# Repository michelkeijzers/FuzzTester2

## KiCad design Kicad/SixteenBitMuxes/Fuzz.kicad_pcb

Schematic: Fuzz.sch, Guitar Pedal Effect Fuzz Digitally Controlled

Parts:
C1: 22uF; CP_Radial_D5.0mm_P2.50mm
H1, H2, H3, H4: MountingHole; MountingHole_3.2mm_M3
J2: TONE_POTS; JST_XH_B4B-XH-A_1x04_P2.50mm_Vertical
J4: VOL POT A100K JST XH; JST_XH_B3B-XH-A_1x03_P2.50mm_Vertical
R1, R2: 100K; R_1206_3216Metric_Pad1.42x1.75mm_HandSolder
R3: 10K; R_1206_3216Metric_Pad1.42x1.75mm_HandSolder

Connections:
/+9V_SAFE: R1.1, R3.1; also elsewhere on the board
/B10K: J2.1, J2.3, R2.1; also elsewhere on the board
/CapacitorsD/CAPACITOR_AUDIO_INPUT: R3.2; also elsewhere on the board
/CapacitorsD/CAPACITOR_AUDIO_OUTPUT: J4.3; also elsewhere on the board
/JACK_OUT_SIGNAL_FROM_FUZZ: J4.2; also elsewhere on the board
/TransistorsB/BASE: R2.2; also elsewhere on the board
/TransistorsC/BASE: R1.2; also elsewhere on the board
GND: H1.1, H4.1; also elsewhere on the board
GNDA: C1.2, H2.1, H3.1, J2.2, J4.1; also elsewhere on the board
unnamed: C1.1, J2.4

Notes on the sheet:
Fuzz Analog Circuit
Audio In/Out and Bypass
Level Shifters
Power Regulator
Micro Controller Unit and User Interface
Mounting Holes

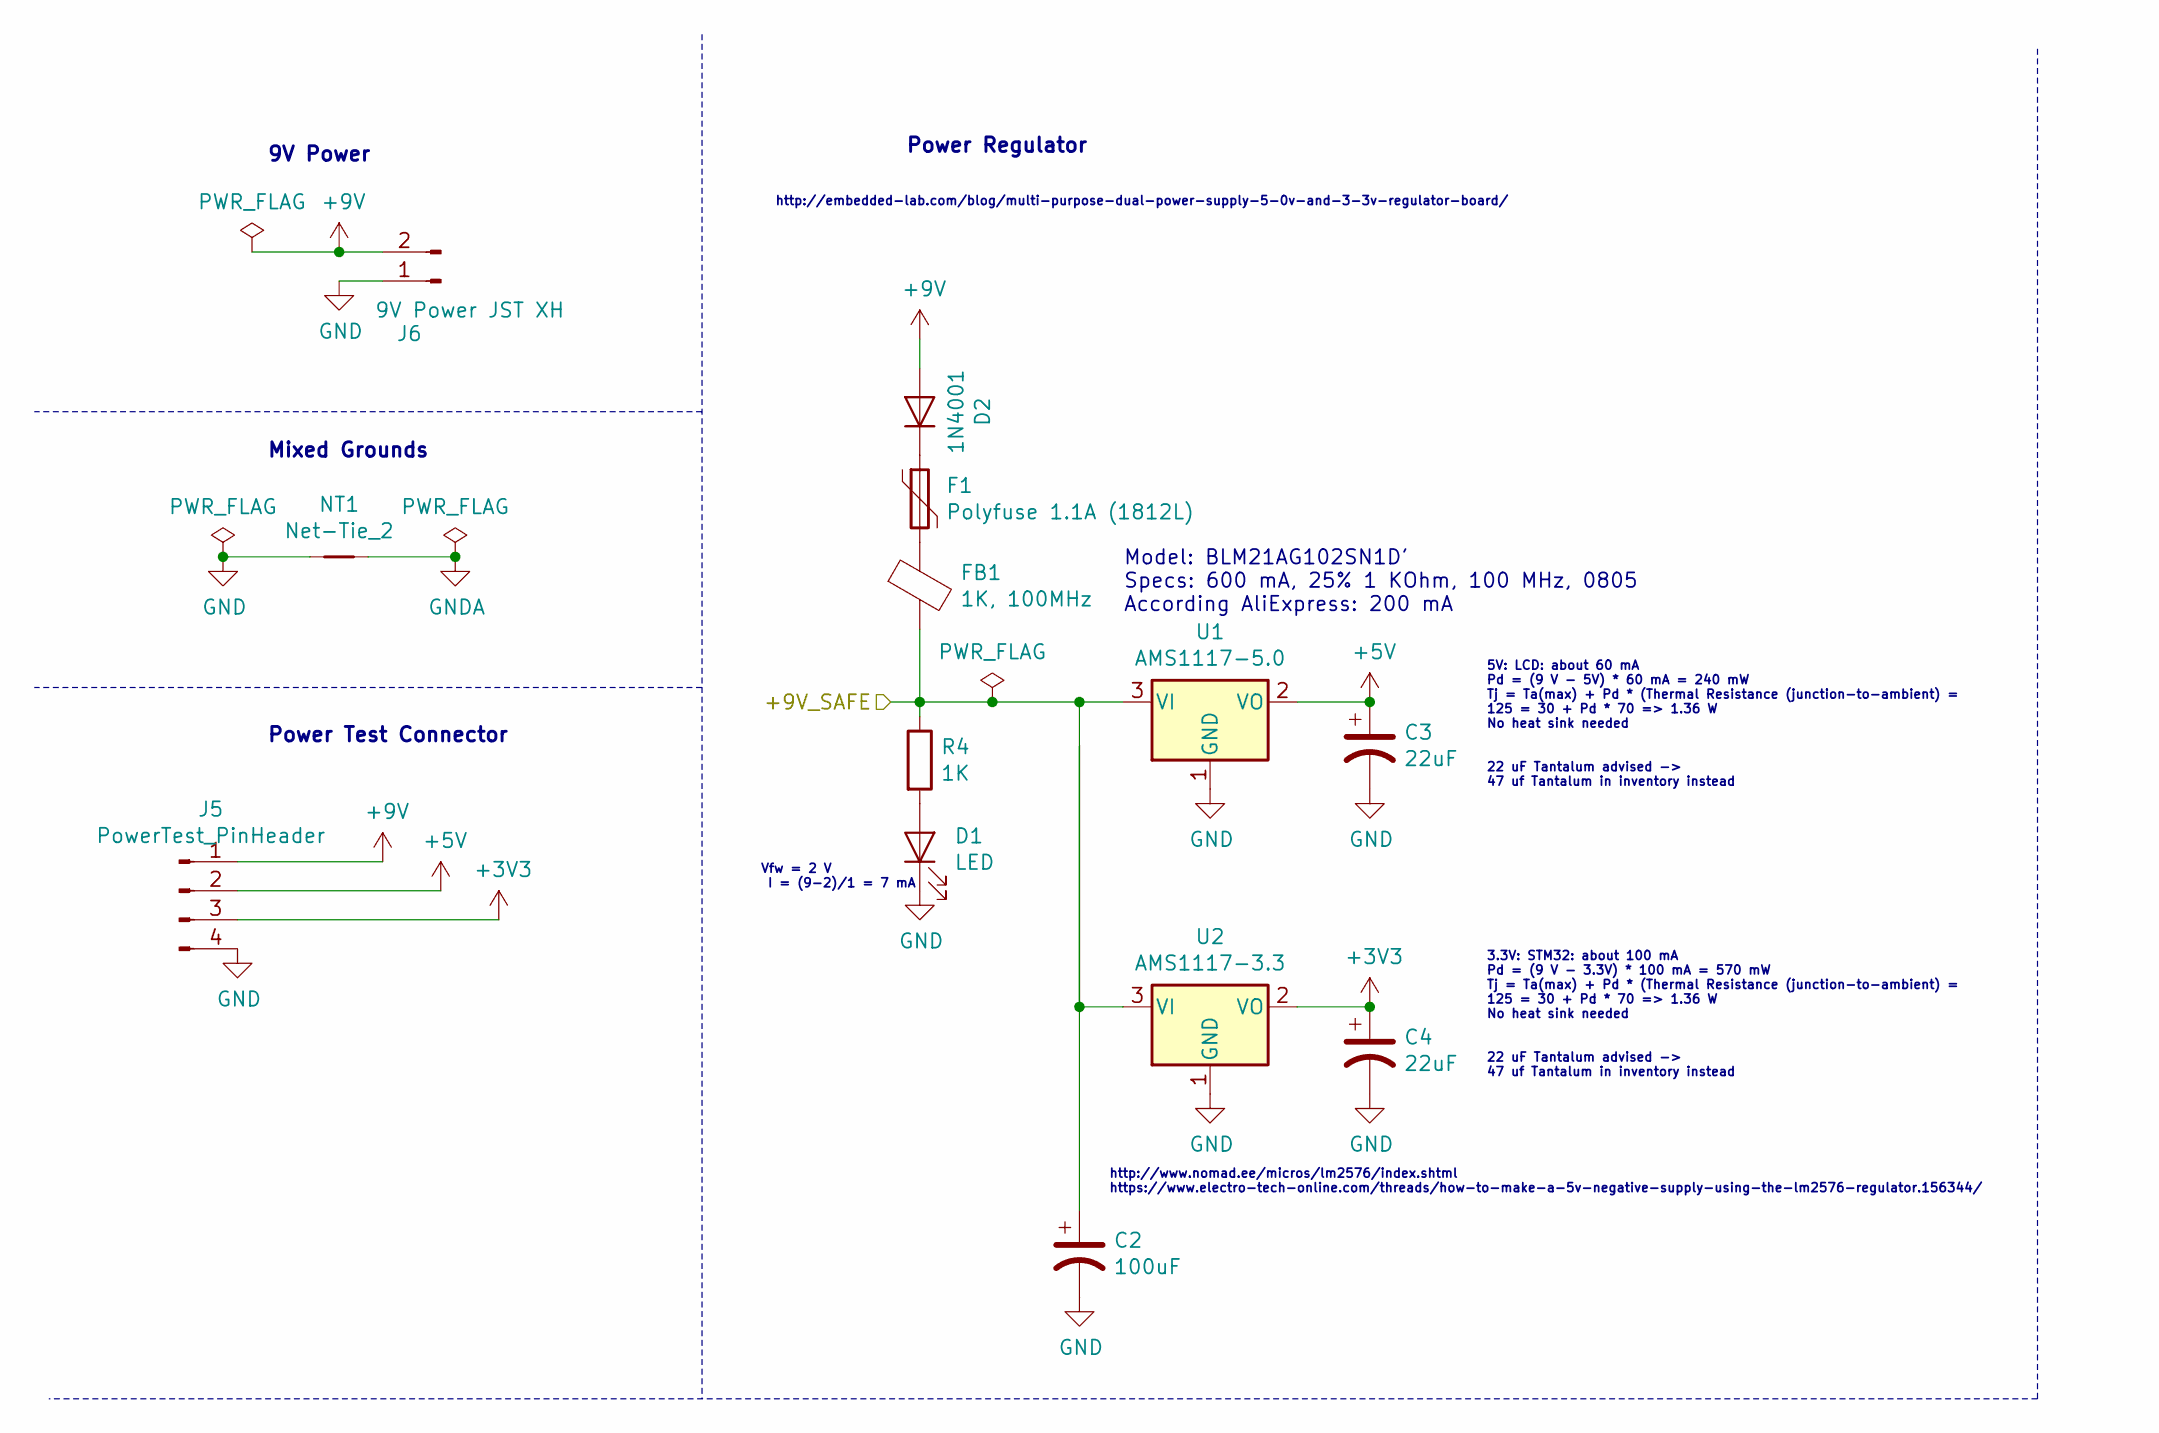
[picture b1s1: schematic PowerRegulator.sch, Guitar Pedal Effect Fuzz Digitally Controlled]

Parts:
C2: 100uF; CP_Radial_D5.0mm_P2.50mm
C3, C4: 22uF; D_SMB_Handsoldering
D1: LED; LED_0805_2012Metric_Pad1.15x1.40mm_HandSolder
D2: 1N4001; D_0805_2012Metric_Pad1.15x1.40mm_HandSolder
F1: Polyfuse 1.1A (1812L); L_1812_4532Metric_Pad1.30x3.40mm_HandSolder
FB1: 1K, 100MHz; L_0805_2012Metric_Pad1.15x1.40mm_HandSolder
J5: PowerTest_PinHeader; PinHeader_1x04_P2.54mm_Vertical
J6: 9V Power JST XH; JST_XH_B2B-XH-A_1x02_P2.50mm_Vertical
NT1: Net-Tie_2; NetTie-2_SMD_Pad2.0mm
R4: 1K; R_0805_2012Metric_Pad1.15x1.40mm_HandSolder
U1: AMS1117-5.0; SOT-223-3_TabPin2
U2: AMS1117-3.3; SOT-223-3_TabPin2

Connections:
+3V3: C4.1, J5.3, U2.2 (VO); also elsewhere on the board
+5V: C3.1, J5.2, U1.2 (VO); also elsewhere on the board
+9V: D2.2 (A), J5.1, J6.2
/+9V_SAFE: C2.1, FB1.2, R4.1, U1.3 (VI), U2.3 (VI); also elsewhere on the board
GND: C2.2, C3.2, C4.2, D1.1 (K), J5.4, J6.1, NT1.1, U1.1 (GND), U2.1 (GND); also elsewhere on the board
GNDA: NT1.2; also elsewhere on the board
unnamed: D1.2 (A), R4.2
unnamed: D2.1 (K), F1.1
unnamed: F1.2, FB1.1

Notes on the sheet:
9V Power
Vfw = 2 V I = (9-2)/1 = 7 mA
5V: LCD: about 60 mA Pd = (9 V - 5V) * 60 mA = 240 mW Tj = Ta(max) + Pd * (Thermal Resistance (junction-to-ambient) = 125 = 30 + Pd * 70 => 1.36 W No heat sink needed
3.3V: STM32: about 100 mA Pd = (9 V - 3.3V) * 100 mA = 570 mW Tj = Ta(max) + Pd * (Thermal Resistance (junction-to-ambient) = 125 = 30 + Pd * 70 => 1.36 W No heat sink needed
Power Regulator
http://embedded-lab.com/blog/multi-purpose-dual-power-supply-5-0v-and-3-3v-regulator-board/
https://www.electro-tech-online.com/threads/how-to-make-a-5v-negative-supply-using-the-lm2576-regulator.156344/
http://www.nomad.ee/micros/lm2576/index.shtml
Power Test Connector
Mixed Grounds
22 uF Tantalum advised -> 47 uf Tantalum in inventory instead
Model: BLM21AG102SN1D' Specs: 600 mA, 25% 1 KOhm, 100 MHz, 0805 According AliExpress: 200 mA

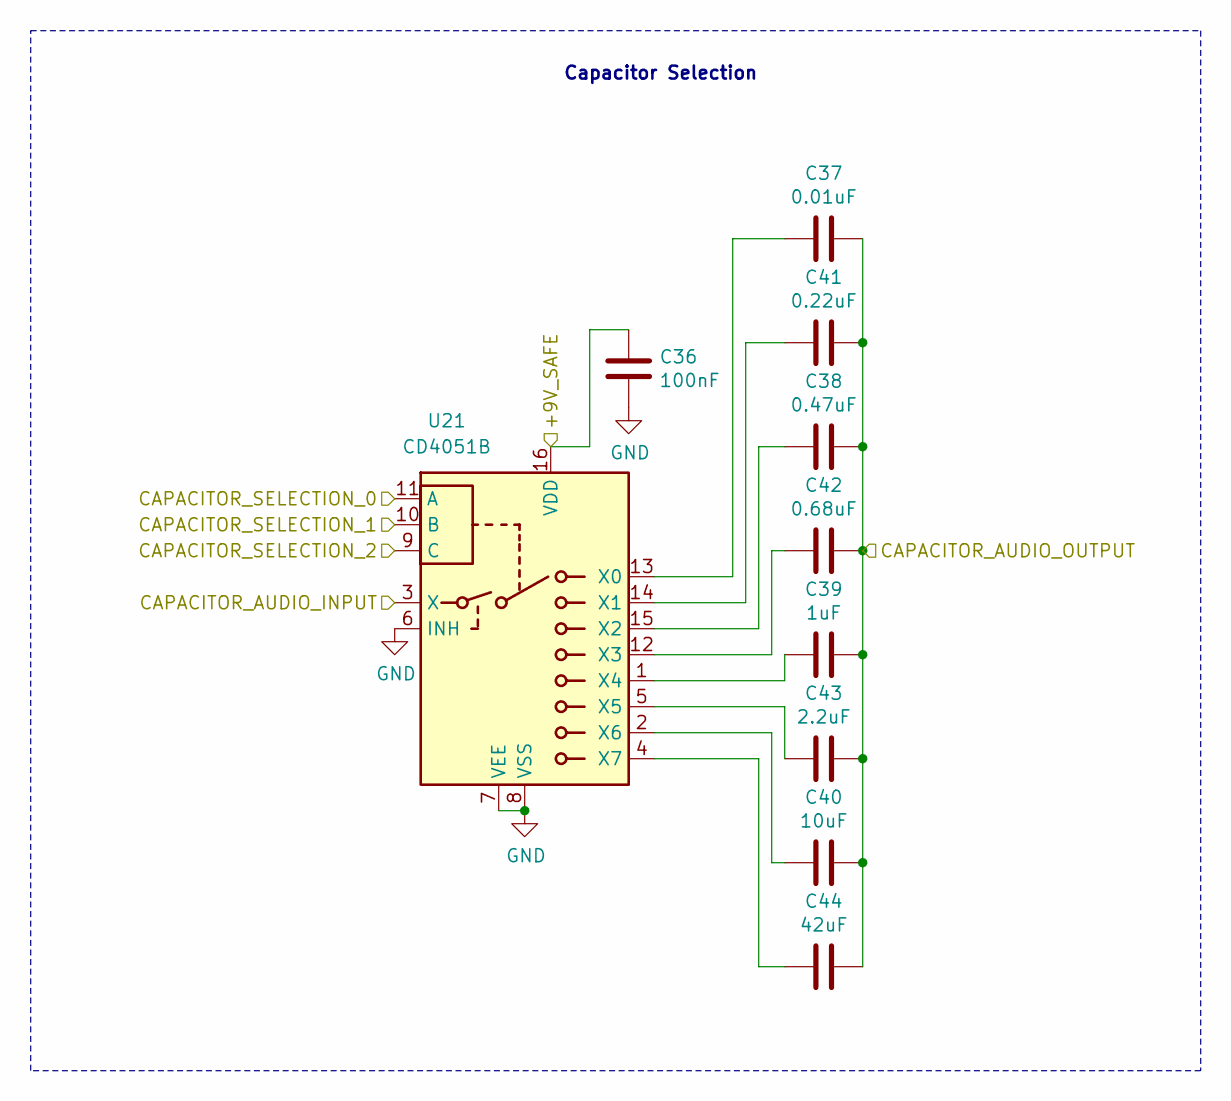
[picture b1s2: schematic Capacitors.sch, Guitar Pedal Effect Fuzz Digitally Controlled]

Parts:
C11: 100nF; C_0805_2012Metric_Pad1.15x1.40mm_HandSolder
C12: 0.01uF; C_0805_2012Metric_Pad1.15x1.40mm_HandSolder
C13: 0.47uF; C_0805_2012Metric_Pad1.15x1.40mm_HandSolder
C14: 1uF; C_0805_2012Metric_Pad1.15x1.40mm_HandSolder
C15: 10uF; C_0805_2012Metric_Pad1.15x1.40mm_HandSolder
C16: 0.22uF; C_0805_2012Metric_Pad1.15x1.40mm_HandSolder
C17: 0.68uF; C_0805_2012Metric_Pad1.15x1.40mm_HandSolder
C18: 2.2uF; C_0805_2012Metric_Pad1.15x1.40mm_HandSolder
C19: 42uF; C_0805_2012Metric_Pad1.15x1.40mm_HandSolder
U4: CD4051B; SOIC-16_3.9x9.9mm_P1.27mm

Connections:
/+9V_SAFE: C11.1, U4.16 (VDD); also elsewhere on the board
/CAPACITOR_A_SELECTION_0: U4.11 (A); also elsewhere on the board
/CAPACITOR_A_SELECTION_1: U4.10 (B); also elsewhere on the board
/CAPACITOR_A_SELECTION_2: U4.9 (C); also elsewhere on the board
/JACK_IN_SIGNAL_THROUGH_FUZZ: U4.3 (X); also elsewhere on the board
/TransistorsB/BASE: C12.1, C13.1, C14.1, C15.1, C16.1, C17.1, C18.1, C19.1; also elsewhere on the board
GND: C11.2, U4.6 (INH), U4.7 (VEE), U4.8 (VSS); also elsewhere on the board
unnamed: C12.2, U4.13 (X0)
unnamed: C13.2, U4.15 (X2)
unnamed: C14.2, U4.1 (X4)
unnamed: C15.2, U4.2 (X6)
unnamed: C16.2, U4.14 (X1)
unnamed: C17.2, U4.12 (X3)
unnamed: C18.2, U4.5 (X5)
unnamed: C19.2, U4.4 (X7)

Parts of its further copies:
C36: 100nF; C_0805_2012Metric_Pad1.15x1.40mm_HandSolder
C37: 0.01uF; C_0805_2012Metric_Pad1.15x1.40mm_HandSolder
C38: 0.47uF; C_0805_2012Metric_Pad1.15x1.40mm_HandSolder
C39: 1uF; C_0805_2012Metric_Pad1.15x1.40mm_HandSolder
C40: 10uF; C_0805_2012Metric_Pad1.15x1.40mm_HandSolder
C41: 0.22uF; C_0805_2012Metric_Pad1.15x1.40mm_HandSolder
C42: 0.68uF; C_0805_2012Metric_Pad1.15x1.40mm_HandSolder
C43: 2.2uF; C_0805_2012Metric_Pad1.15x1.40mm_HandSolder
C44: 42uF; C_0805_2012Metric_Pad1.15x1.40mm_HandSolder

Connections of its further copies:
/+9V_SAFE: C36.1; also elsewhere on the board
/CapacitorsD/CAPACITOR_AUDIO_OUTPUT: C37.1, C38.1, C39.1, C40.1, C41.1, C42.1, C43.1, C44.1; also elsewhere on the board
GND: C36.2; also elsewhere on the board
unnamed 139: C37.2; also elsewhere on the board
unnamed 140: C38.2; also elsewhere on the board
unnamed 141: C39.2; also elsewhere on the board
unnamed 142: C40.2; also elsewhere on the board
unnamed 143: C41.2; also elsewhere on the board
unnamed 144: C42.2; also elsewhere on the board
unnamed 145: C43.2; also elsewhere on the board
unnamed 146: C44.2; also elsewhere on the board

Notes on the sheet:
Capacitor Selection

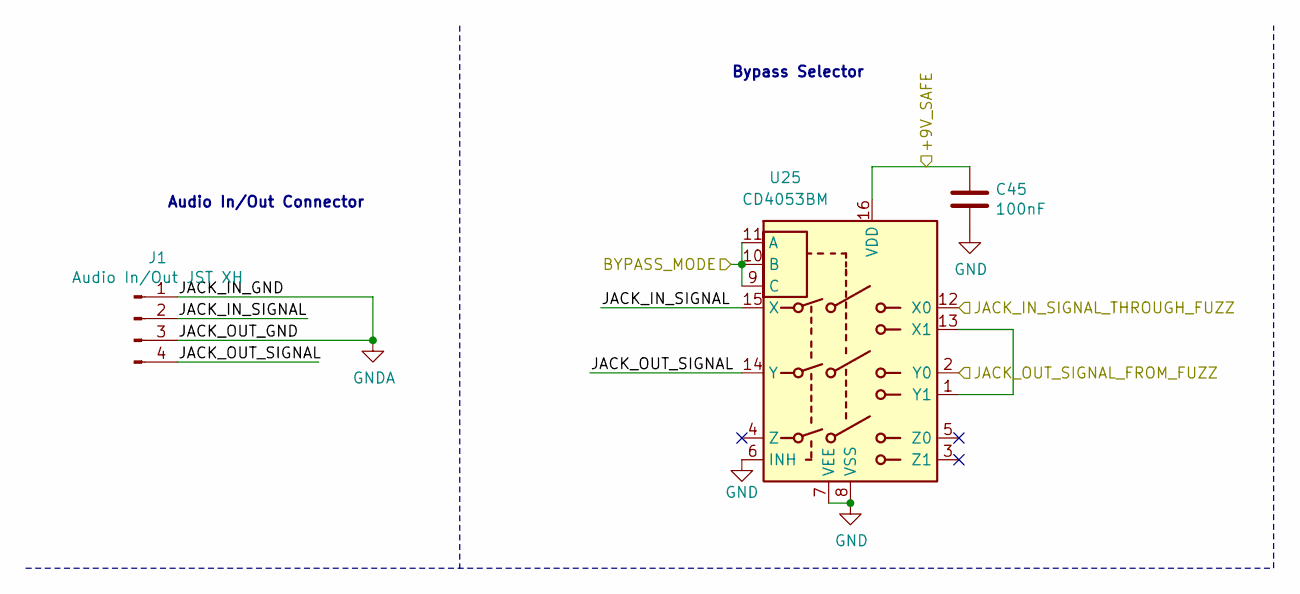
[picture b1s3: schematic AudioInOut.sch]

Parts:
C45: 100nF; C_0805_2012Metric_Pad1.15x1.40mm_HandSolder
J1: Audio In/Out JST XH; JST_XH_B4B-XH-A_1x04_P2.50mm_Vertical
U25: CD4053BM; SOIC-16_3.9x9.9mm_P1.27mm

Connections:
/+9V_SAFE: C45.1, U25.16 (VDD); also elsewhere on the board
/AudioInOut/JACK_IN_SIGNAL: J1.2, U25.15 (X)
/AudioInOut/JACK_OUT_SIGNAL: J1.4, U25.14 (Y)
/BYPASS_MODE: U25.9 (C), U25.10 (B), U25.11 (A); also elsewhere on the board
/JACK_IN_SIGNAL_THROUGH_FUZZ: U25.12 (X0); also elsewhere on the board
/JACK_OUT_SIGNAL_FROM_FUZZ: U25.2 (Y0); also elsewhere on the board
GND: C45.2, U25.6 (INH), U25.7 (VEE), U25.8 (VSS); also elsewhere on the board
GNDA: J1.1, J1.3; also elsewhere on the board
unnamed: U25.1 (Y1), U25.13 (X1)

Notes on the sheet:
Bypass Selector
Audio In/Out Connector

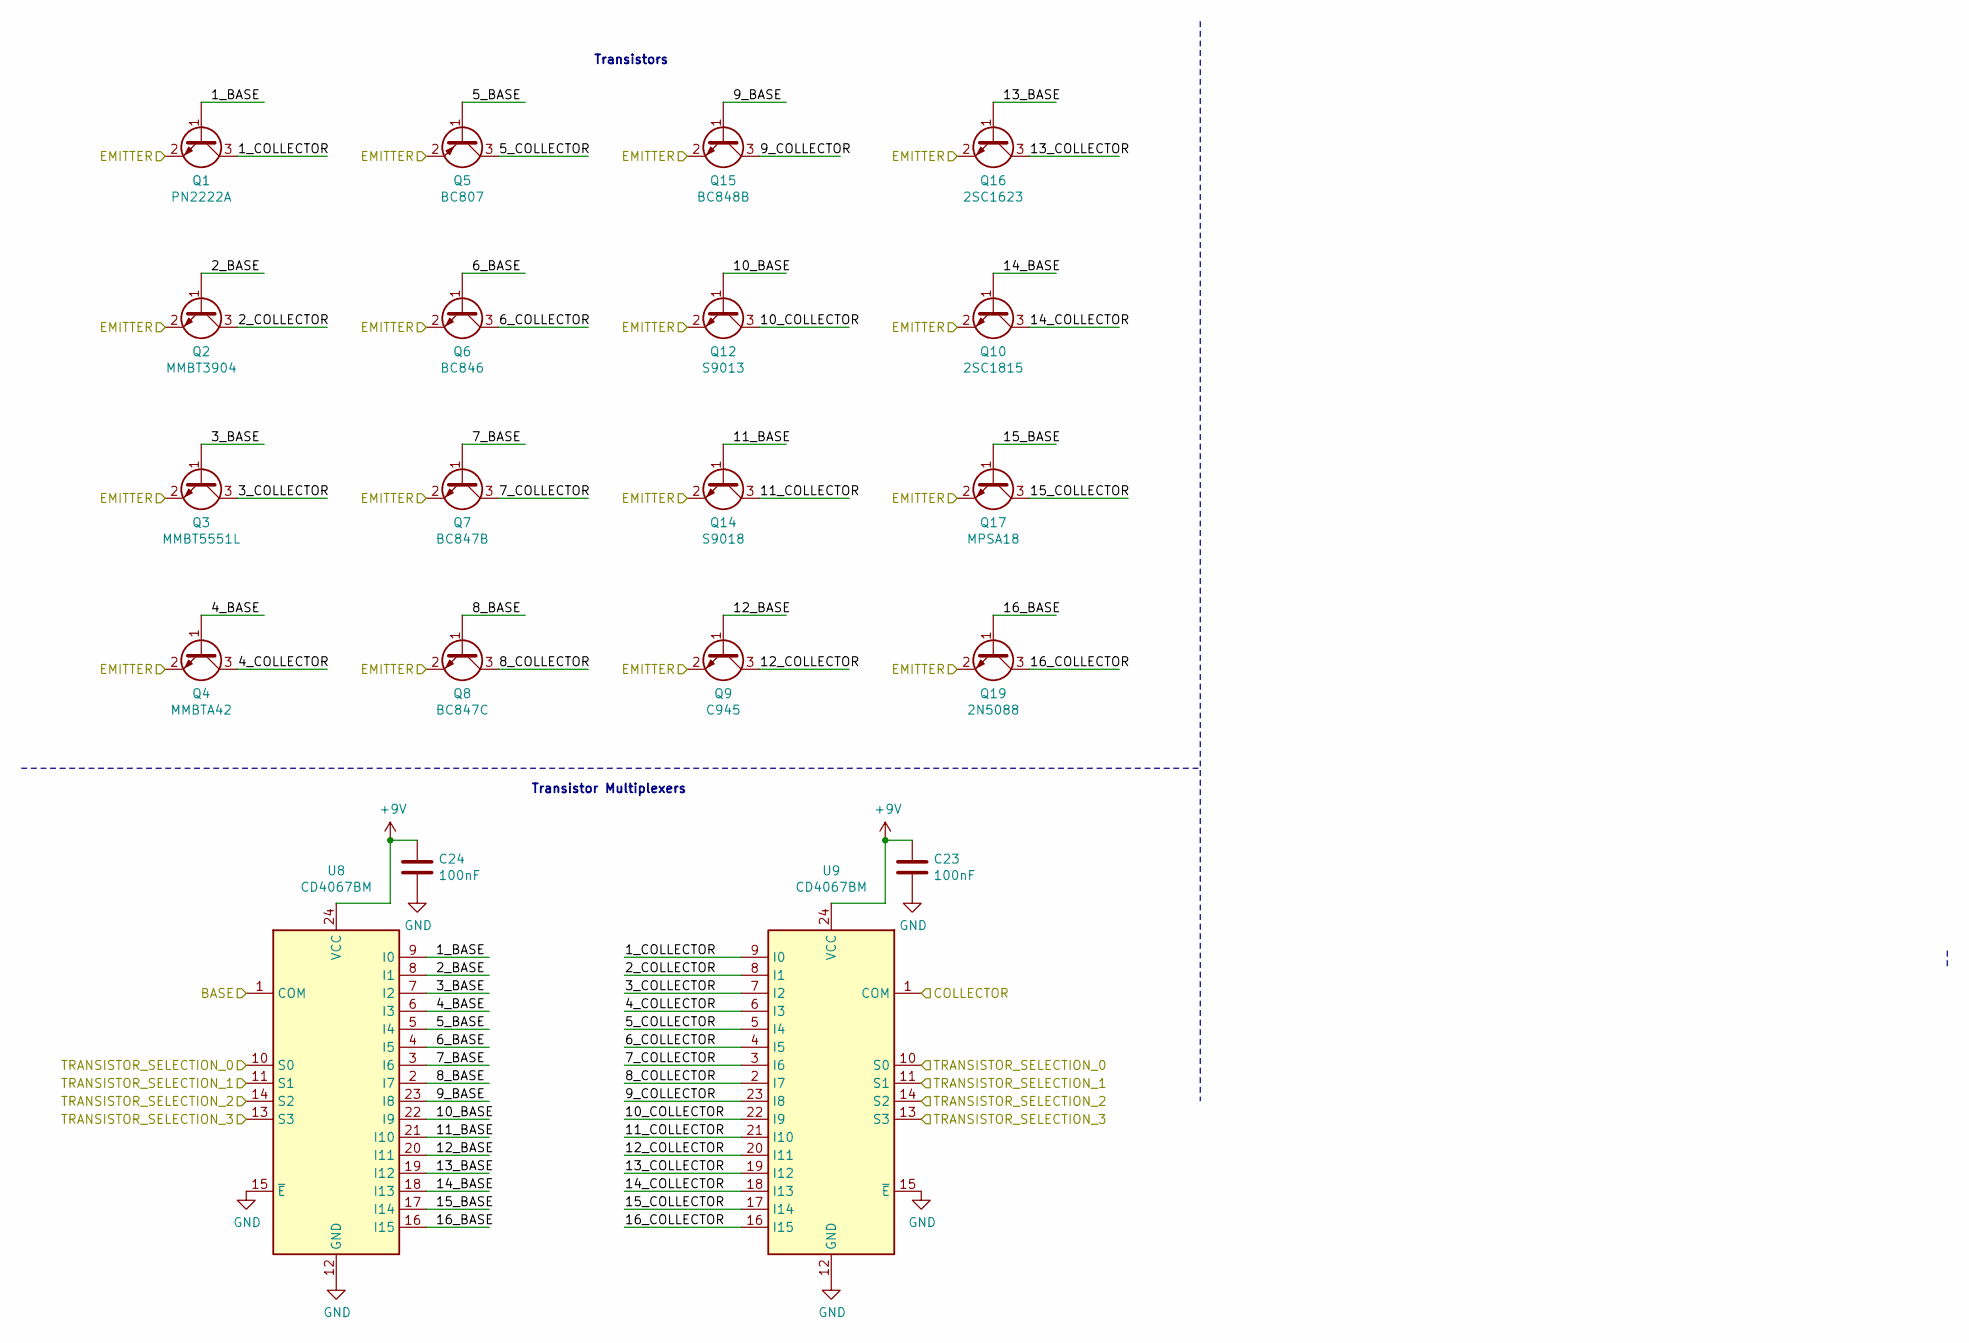
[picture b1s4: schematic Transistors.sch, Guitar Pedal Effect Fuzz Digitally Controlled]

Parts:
C23, C24: 100nF; C_0805_2012Metric_Pad1.15x1.40mm_HandSolder
Q1: PN2222A; SOT-23_Handsoldering
Q2: MMBT3904; SOT-23_Handsoldering
Q3: MMBT5551L; SOT-23_Handsoldering
Q4: MMBTA42; SOT-23_Handsoldering
Q5: BC807; SOT-23_Handsoldering
Q6: BC846; SOT-23_Handsoldering
Q7: BC847B; SOT-23_Handsoldering
Q8: BC847C; SOT-23_Handsoldering
Q9: C945; SOT-23_Handsoldering
Q10: 2SC1815; SOT-23_Handsoldering
Q12: S9013; SOT-23_Handsoldering
Q14: S9018; SOT-23_Handsoldering
Q15: BC848B; SOT-23_Handsoldering
Q16: 2SC1623; SOT-23_Handsoldering
Q17: MPSA18; TO-92_Inline
Q19: 2N5088; TO-92_Inline
U8, U9: CD4067BM; SOIC-24W_7.5x15.4mm_P1.27mm

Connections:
/+9V_SAFE: C23.1, C24.1, U8.24 (VCC), U9.24 (VCC); also elsewhere on the board
/TRANSISTOR_B_SELECTION_0: U8.10 (S0), U9.10 (S0); also elsewhere on the board
/TRANSISTOR_B_SELECTION_1: U8.11 (S1), U9.11 (S1); also elsewhere on the board
/TRANSISTOR_B_SELECTION_2: U8.14 (S2), U9.14 (S2); also elsewhere on the board
/TRANSISTOR_B_SELECTION_3: U8.13 (S3), U9.13 (S3); also elsewhere on the board
/TransistorsB/1_BASE: Q1.1 (B), U8.9 (I0)
/TransistorsB/1_COLLECTOR: Q1.3 (C), U9.9 (I0)
/TransistorsB/2_BASE: Q2.1 (B), U8.8 (I1)
/TransistorsB/2_COLLECTOR: Q2.3 (C), U9.8 (I1)
/TransistorsB/3_BASE: Q3.1 (B), U8.7 (I2)
/TransistorsB/3_COLLECTOR: Q3.3 (C), U9.7 (I2)
/TransistorsB/4_BASE: Q4.1 (B), U8.6 (I3)
/TransistorsB/4_COLLECTOR: Q4.3 (C), U9.6 (I3)
/TransistorsB/5_BASE: Q5.1 (B), U8.5 (I4)
/TransistorsB/5_COLLECTOR: Q5.3 (C), U9.5 (I4)
/TransistorsB/6_BASE: Q6.1 (B), U8.4 (I5)
/TransistorsB/6_COLLECTOR: Q6.3 (C), U9.4 (I5)
/TransistorsB/7_BASE: Q7.1 (B), U8.3 (I6)
/TransistorsB/7_COLLECTOR: Q7.3 (C), U9.3 (I6)
/TransistorsB/8_BASE: Q8.1 (B), U8.2 (I7)
/TransistorsB/8_COLLECTOR: Q8.3 (C), U9.2 (I7)
/TransistorsB/9_BASE: Q15.1 (B), U8.23 (I8)
/TransistorsB/9_COLLECTOR: Q15.3 (C), U9.23 (I8)
/TransistorsB/10_BASE: Q12.1 (B), U8.22 (I9)
/TransistorsB/10_COLLECTOR: Q12.3 (C), U9.22 (I9)
/TransistorsB/11_BASE: Q14.1 (B), U8.21 (I10)
/TransistorsB/11_COLLECTOR: Q14.3 (C), U9.21 (I10)
/TransistorsB/12_BASE: Q9.1 (B), U8.20 (I11)
/TransistorsB/12_COLLECTOR: Q9.3 (C), U9.20 (I11)
/TransistorsB/13_BASE: Q16.1 (B), U8.19 (I12)
/TransistorsB/13_COLLECTOR: Q16.3 (C), U9.19 (I12)
/TransistorsB/14_BASE: Q10.1 (B), U8.18 (I13)
/TransistorsB/14_COLLECTOR: Q10.3 (C), U9.18 (I13)
/TransistorsB/15_BASE: Q17.1 (B), U8.17 (I14)
/TransistorsB/15_COLLECTOR: Q17.3 (C), U9.17 (I14)
/TransistorsB/16_BASE: Q19.1 (B), U8.16 (I15)
/TransistorsB/16_COLLECTOR: Q19.3 (C), U9.16 (I15)
/TransistorsB/BASE: U8.1 (COM); also elsewhere on the board
/TransistorsC/BASE: U9.1 (COM); also elsewhere on the board
GND: C23.2, C24.2, U8.12 (GND), U8.15 (~E), U9.12 (GND), U9.15 (~E); also elsewhere on the board
GNDA: Q1.2 (E), Q2.2 (E), Q3.2 (E), Q4.2 (E), Q5.2 (E), Q6.2 (E), Q7.2 (E), Q8.2 (E), Q9.2 (E), Q10.2 (E), Q12.2 (E), Q14.2 (E), Q15.2 (E), Q16.2 (E), Q17.2 (E), Q19.2 (E); also elsewhere on the board

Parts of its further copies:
C21, C22, C31: 100nF; C_0805_2012Metric_Pad1.15x1.40mm_HandSolder
Q11: PN2222A; SOT-23_Handsoldering
Q13: MMBT3904; SOT-23_Handsoldering
Q18: MMBT5551L; SOT-23_Handsoldering
Q20: MMBTA42; SOT-23_Handsoldering
Q24: BC847C; SOT-23_Handsoldering
Q25, Q35: BC848B; SOT-23_Handsoldering
Q26: S9013; SOT-23_Handsoldering
Q27, Q34: S9018; SOT-23_Handsoldering
Q28: C945; SOT-23_Handsoldering
Q30: 2SC1815; SOT-23_Handsoldering
Q31, Q37: MPSA18; TO-92_Inline
Q36: 2SC1623; SOT-23_Handsoldering
Q39: 2N5088; TO-92_Inline
U6, U7: CD4067BM; SOIC-24W_7.5x15.4mm_P1.27mm

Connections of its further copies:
/+9V_SAFE: C21.1, C22.1, U6.24 (VCC), U7.24 (VCC); also elsewhere on the board
/B10K: Q11.2 (E), Q13.2 (E), Q18.2 (E), Q20.2 (E), Q24.2 (E), Q25.2 (E), Q26.2 (E), Q27.2 (E), Q28.2 (E), Q30.2 (E), Q31.2 (E); also elsewhere on the board
/CapacitorsD/CAPACITOR_AUDIO_INPUT: U7.1 (COM); also elsewhere on the board
/TRANSISTOR_C_SELECTION_0: U6.10 (S0), U7.10 (S0); also elsewhere on the board
/TRANSISTOR_C_SELECTION_1: U6.11 (S1), U7.11 (S1); also elsewhere on the board
/TRANSISTOR_C_SELECTION_2: U6.14 (S2), U7.14 (S2); also elsewhere on the board
/TRANSISTOR_C_SELECTION_3: U6.13 (S3), U7.13 (S3); also elsewhere on the board
/TransistorsC/1_BASE: Q11.1 (B), U6.9 (I0)
/TransistorsC/1_COLLECTOR: Q11.3 (C), U7.9 (I0)
/TransistorsC/2_BASE: Q13.1 (B), U6.8 (I1)
/TransistorsC/2_COLLECTOR: Q13.3 (C), U7.8 (I1)
/TransistorsC/3_BASE: Q18.1 (B), U6.7 (I2)
/TransistorsC/3_COLLECTOR: Q18.3 (C), U7.7 (I2)
/TransistorsC/4_BASE: Q20.1 (B), U6.6 (I3)
/TransistorsC/4_COLLECTOR: Q20.3 (C), U7.6 (I3)
/TransistorsC/5_BASE: U6.5 (I4); also elsewhere on the board
/TransistorsC/5_COLLECTOR: U7.5 (I4); also elsewhere on the board
/TransistorsC/6_BASE: U6.4 (I5); also elsewhere on the board
/TransistorsC/6_COLLECTOR: U7.4 (I5); also elsewhere on the board
/TransistorsC/7_BASE: U6.3 (I6); also elsewhere on the board
/TransistorsC/7_COLLECTOR: U7.3 (I6); also elsewhere on the board
/TransistorsC/8_BASE: Q24.1 (B), U6.2 (I7)
/TransistorsC/8_COLLECTOR: Q24.3 (C), U7.2 (I7)
/TransistorsC/9_BASE: Q25.1 (B), U6.23 (I8)
/TransistorsC/9_COLLECTOR: Q25.3 (C), U7.23 (I8)
/TransistorsC/10_BASE: Q26.1 (B), U6.22 (I9)
/TransistorsC/10_COLLECTOR: Q26.3 (C), U7.22 (I9)
/TransistorsC/11_BASE: Q27.1 (B), U6.21 (I10)
/TransistorsC/11_COLLECTOR: Q27.3 (C), U7.21 (I10)
/TransistorsC/12_BASE: Q28.1 (B), U6.20 (I11)
/TransistorsC/12_COLLECTOR: Q28.3 (C), U7.20 (I11)
/TransistorsC/13_BASE: U6.19 (I12); also elsewhere on the board
/TransistorsC/13_COLLECTOR: U7.19 (I12); also elsewhere on the board
/TransistorsC/14_BASE: Q30.1 (B), U6.18 (I13)
/TransistorsC/14_COLLECTOR: Q30.3 (C), U7.18 (I13)
/TransistorsC/15_BASE: Q31.1 (B), U6.17 (I14)
/TransistorsC/15_COLLECTOR: Q31.3 (C), U7.17 (I14)
/TransistorsC/16_BASE: U6.16 (I15); also elsewhere on the board
/TransistorsC/16_COLLECTOR: U7.16 (I15); also elsewhere on the board
/TransistorsC/BASE: U6.1 (COM); also elsewhere on the board
GND: C21.2, C22.2, U6.12 (GND), U6.15 (~E), U7.12 (GND), U7.15 (~E); also elsewhere on the board

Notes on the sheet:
Transistors
Transistor Multiplexers

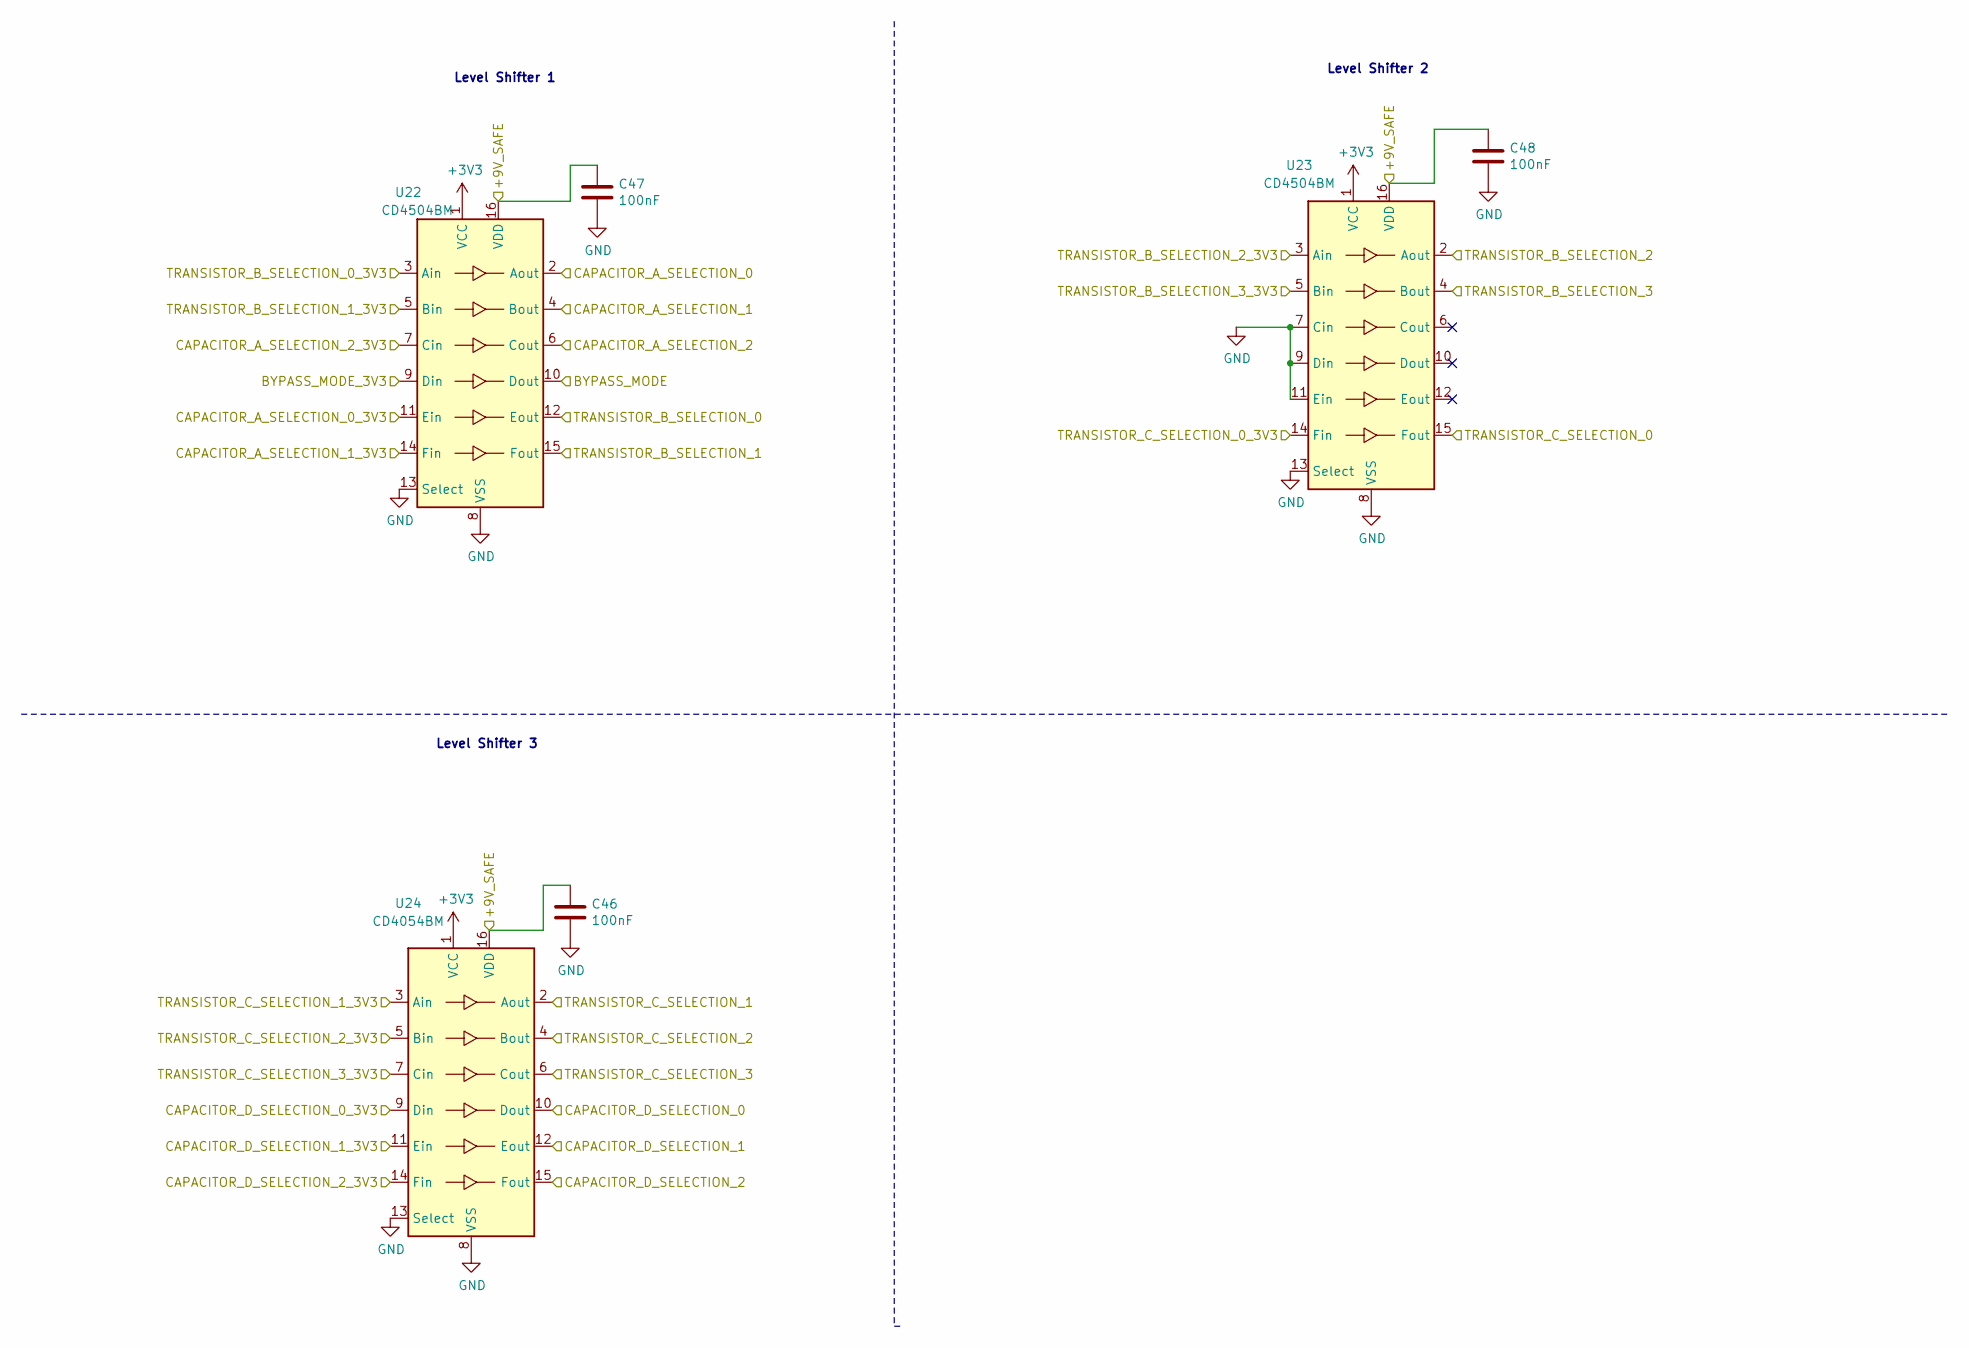
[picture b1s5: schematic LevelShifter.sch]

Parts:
C46, C47, C48: 100nF; C_0805_2012Metric_Pad1.15x1.40mm_HandSolder
U22, U23: CD4504BM; SOIC-16_3.9x9.9mm_P1.27mm
U24: CD4054BM; SOIC-16_3.9x9.9mm_P1.27mm

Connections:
+3V3: U22.1 (VCC), U23.1 (VCC), U24.1 (VCC); also elsewhere on the board
/+9V_SAFE: C46.1, C47.1, C48.1, U22.16 (VDD), U23.16 (VDD), U24.16 (VDD); also elsewhere on the board
/BYPASS_MODE: U22.10 (Dout); also elsewhere on the board
/BYPASS_MODE_3V3: U22.9 (Din); also elsewhere on the board
/CAPACITOR_A_SELECTION_0: U22.2 (Aout); also elsewhere on the board
/CAPACITOR_A_SELECTION_0_3V3: U22.11 (Ein); also elsewhere on the board
/CAPACITOR_A_SELECTION_1: U22.4 (Bout); also elsewhere on the board
/CAPACITOR_A_SELECTION_1_3V3: U22.14 (Fin); also elsewhere on the board
/CAPACITOR_A_SELECTION_2: U22.6 (Cout); also elsewhere on the board
/CAPACITOR_A_SELECTION_2_3V3: U22.7 (Cin); also elsewhere on the board
/CAPACITOR_D_SELECTION_0: U24.10 (Dout); also elsewhere on the board
/CAPACITOR_D_SELECTION_0_3V3: U24.9 (Din); also elsewhere on the board
/CAPACITOR_D_SELECTION_1: U24.12 (Eout); also elsewhere on the board
/CAPACITOR_D_SELECTION_1_3V3: U24.11 (Ein); also elsewhere on the board
/CAPACITOR_D_SELECTION_2: U24.15 (Fout); also elsewhere on the board
/CAPACITOR_D_SELECTION_2_3V3: U24.14 (Fin); also elsewhere on the board
/TRANSISTOR_B_SELECTION_0: U22.12 (Eout); also elsewhere on the board
/TRANSISTOR_B_SELECTION_0_3V3: U22.3 (Ain); also elsewhere on the board
/TRANSISTOR_B_SELECTION_1: U22.15 (Fout); also elsewhere on the board
/TRANSISTOR_B_SELECTION_1_3V3: U22.5 (Bin); also elsewhere on the board
/TRANSISTOR_B_SELECTION_2: U23.2 (Aout); also elsewhere on the board
/TRANSISTOR_B_SELECTION_2_3V3: U23.3 (Ain); also elsewhere on the board
/TRANSISTOR_B_SELECTION_3: U23.4 (Bout); also elsewhere on the board
/TRANSISTOR_B_SELECTION_3_3V3: U23.5 (Bin); also elsewhere on the board
/TRANSISTOR_C_SELECTION_0: U23.15 (Fout); also elsewhere on the board
/TRANSISTOR_C_SELECTION_0_3V3: U23.14 (Fin); also elsewhere on the board
/TRANSISTOR_C_SELECTION_1: U24.2 (Aout); also elsewhere on the board
/TRANSISTOR_C_SELECTION_1_3V3: U24.3 (Ain); also elsewhere on the board
/TRANSISTOR_C_SELECTION_2: U24.4 (Bout); also elsewhere on the board
/TRANSISTOR_C_SELECTION_2_3V3: U24.5 (Bin); also elsewhere on the board
/TRANSISTOR_C_SELECTION_3: U24.6 (Cout); also elsewhere on the board
/TRANSISTOR_C_SELECTION_3_3V3: U24.7 (Cin); also elsewhere on the board
GND: C46.2, C47.2, C48.2, U22.8 (VSS), U22.13 (Select), U23.7 (Cin), U23.8 (VSS), U23.9 (Din), U23.11 (Ein), U23.13 (Select), U24.8 (VSS), U24.13 (Select); also elsewhere on the board

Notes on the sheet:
Level Shifter 1
Level Shifter 2
Level Shifter 3

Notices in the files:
FuzzTester/Core/Src/main.cpp:
© Copyright (c) 2020 STMicroelectronics.
All rights reserved.
This software component is licensed by ST under BSD 3-Clause license,
the "License"; You may not use this file except in compliance with the
License. You may obtain a copy of the License at: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
(C) COPYRIGHT STMicroelectronics *****END OF FILE
FuzzTester/Kicad/Fuzz.kicad_pcb:
©2020 Michel Keijzers
Kicad/SixteenBitMuxes/Fuzz.kicad_pcb:
©2020
